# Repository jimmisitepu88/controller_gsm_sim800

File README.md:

# controller_gsm_sim800
circuit controller sim800 to control relay with SMS
I create this pcb with eagle file for controller relay with sms. 
for support library we use 
https://github.com/cristiansteib/Sim800l/blob/master/Sim800l.h

Thanks

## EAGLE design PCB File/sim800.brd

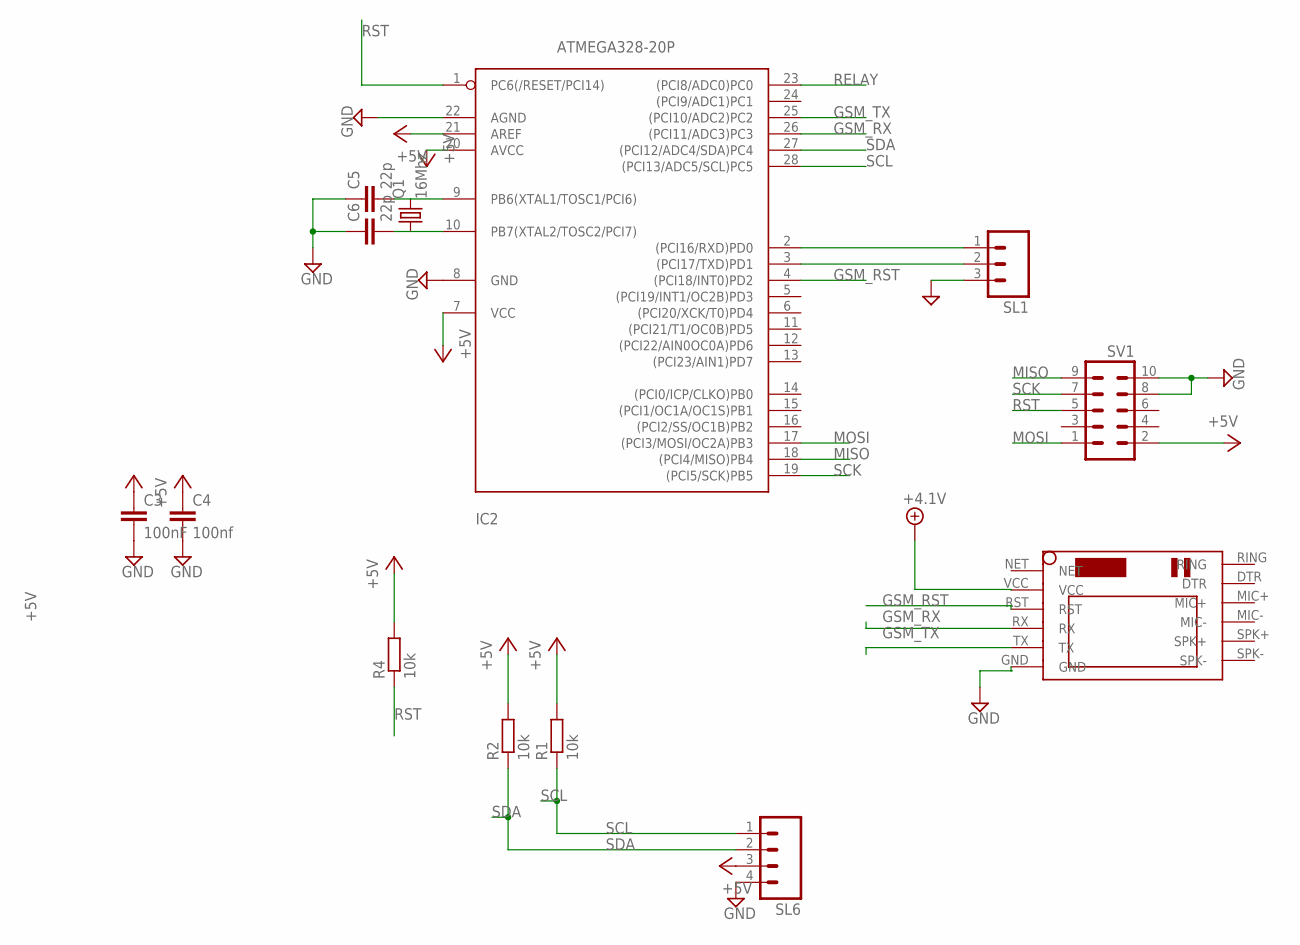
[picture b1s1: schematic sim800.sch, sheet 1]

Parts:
C3: 100nF; C050-025X075
C4: 100nf; C050-025X075
C5, C6: 22p; C025-025X050
IC2: ATMEGA328-20P; DIL28-3
Q1: 16Mhz; HC49U-V
R1, R2, R4: 10k; 0207/10
SL1: M03; 03P
SL6: M04; 04P
SV1: ML10
U$1: SIM800LMODULE

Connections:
+4.1V: U$1.VCC; also elsewhere on the board
+5V: C3.1, C4.1, IC2.7 (VCC), IC2.20 (AVCC), IC2.21 (AREF), R1.2, R2.2, R4.2, SL6.3, SV1.2; also elsewhere on the board
GND: C3.2, C4.2, C5.1, C6.1, IC2.8 (GND), IC2.22 (AGND), SL1.3, SL6.4, SV1.8, SV1.10, U$1.GND; also elsewhere on the board
GSM_RST: IC2.4 ((PCI18/INT0)PD2), U$1.RST
GSM_RX: IC2.26 ((PCI11/ADC3)PC3), U$1.RX
GSM_TX: IC2.25 ((PCI10/ADC2)PC2), U$1.TX
MISO: IC2.18 ((PCI4/MISO)PB4), SV1.9
MOSI: IC2.17 ((PCI3/MOSI/OC2A)PB3), SV1.1
unnamed: C5.2, IC2.9 (PB6(XTAL1/TOSC1/PCI6)), Q1.2
unnamed: C6.2, IC2.10 (PB7(XTAL2/TOSC2/PCI7)), Q1.1
unnamed: IC2.2 ((PCI16/RXD)PD0), SL1.1
unnamed: IC2.3 ((PCI17/TXD)PD1), SL1.2
RELAY: IC2.23 ((PCI8/ADC0)PC0); also elsewhere on the board
RST: IC2.1 (PC6(/RESET/PCI14)), R4.1, SV1.5
SCK: IC2.19 ((PCI5/SCK)PB5), SV1.7
SCL: IC2.28 ((PCI13/ADC5/SCL)PC5), R1.1, SL6.1
SDA: IC2.27 ((PCI12/ADC4/SDA)PC4), R2.1, SL6.2

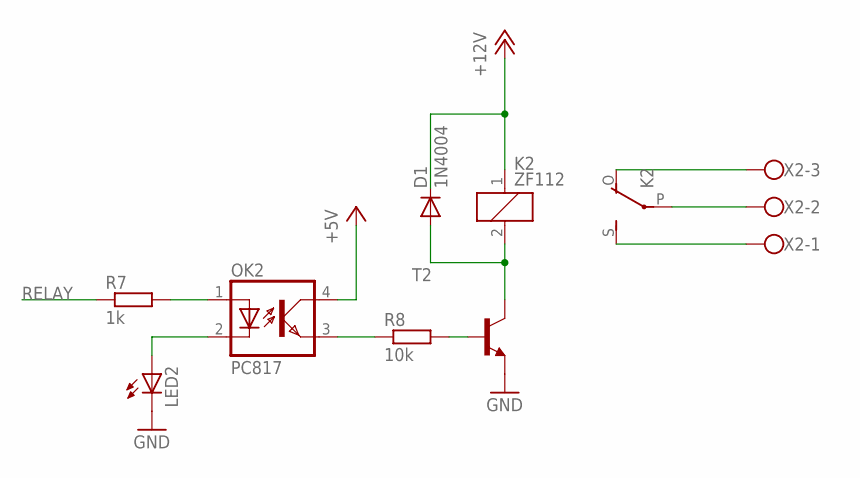
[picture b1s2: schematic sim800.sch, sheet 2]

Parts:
D1: 1N4004; DO41-10
K2: ZF112
LED2: LED3MM
OK2: PC817; DIL04
R7: 1k; 0207/10
R8: 10k; 0207/10
T2: -NPN-TO92-EBC; TO92-EBC
X2: W237-103

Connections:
+5V: OK2.4 (COL); also elsewhere on the board
+12V: D1.C, K2.1; also elsewhere on the board
GND: LED2.K (C), T2.E; also elsewhere on the board
unnamed: OK2.1 (A), R7.2
unnamed: LED2.A, OK2.2 (C)
unnamed: OK2.3 (EMIT), R8.1
unnamed: R8.2, T2.B
unnamed: D1.A, K2.2, T2.C
unnamed: K2.P, X2.2
unnamed: K2.S, X2.1
unnamed: K2.O, X2.3
RELAY: R7.1; also elsewhere on the board

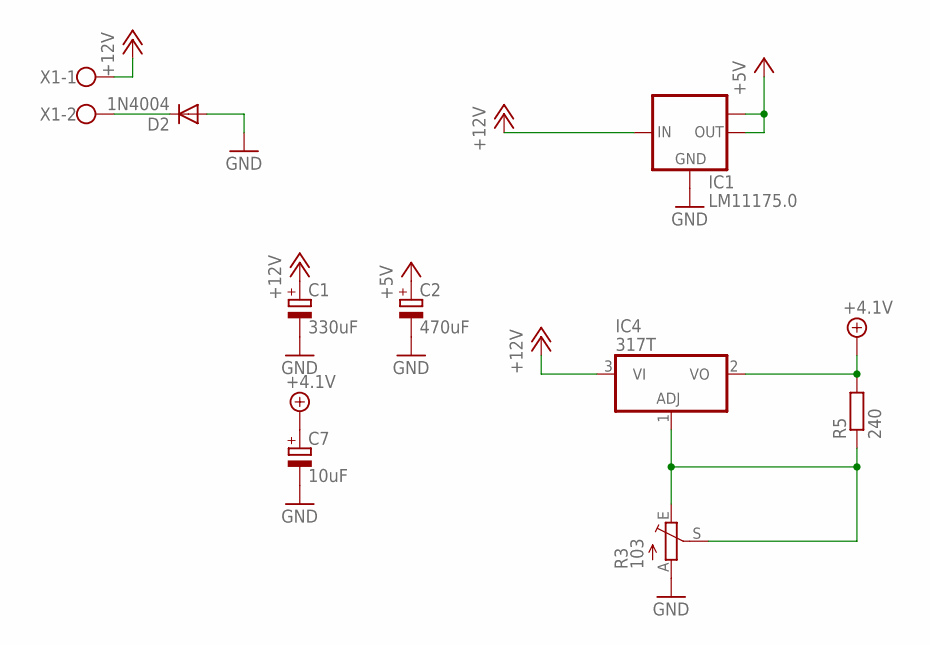
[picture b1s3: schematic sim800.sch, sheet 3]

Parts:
C1: 330uF; E3,5-8
C2: 470uF; E3,5-8
C7: 10uF; E2,5-6
D2: 1N4004; DO41-10
IC1: LM11175.0; SOT223
IC4: 317T; TO220H
R3: 103; CA6V
R5: 240; 0207/10
X1: W237-102

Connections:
+4.1V: C7.+, IC4.2 (VO), R5.2; also elsewhere on the board
+5V: C2.+, IC1.2 (OUT), IC1.TAB (OUT1); also elsewhere on the board
+12V: C1.+, IC1.3 (IN), IC4.3 (VI), X1.1; also elsewhere on the board
GND: C1.-, C2.-, C7.-, D2.A, IC1.1 (GND), R3.A; also elsewhere on the board
unnamed: D2.C, X1.2
unnamed: IC4.1 (ADJ), R3.E, R3.S, R5.1

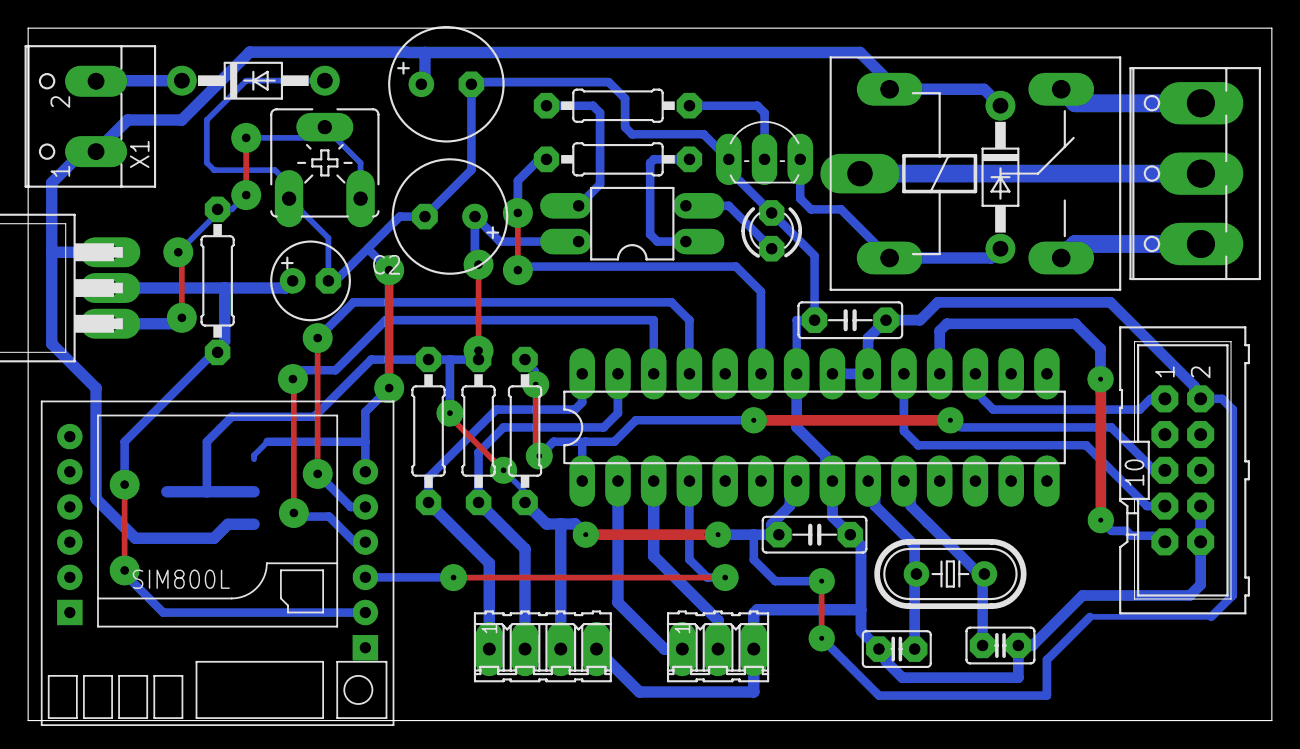
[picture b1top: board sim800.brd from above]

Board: 2 copper layers, 88.4 x 49.2 mm, 30 parts (1 on the bottom side), 28 nets.
